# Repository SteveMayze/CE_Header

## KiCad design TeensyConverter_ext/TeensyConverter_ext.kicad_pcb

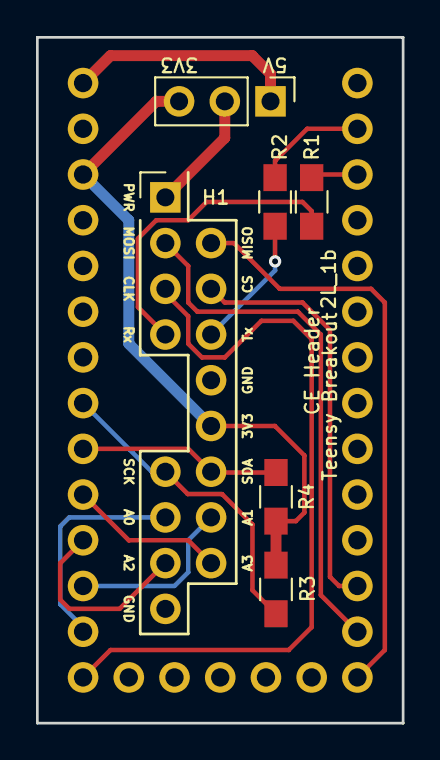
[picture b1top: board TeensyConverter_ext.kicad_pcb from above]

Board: 2 copper layers, 20.3 x 38.1 mm, 7 parts (1 on the bottom side), 18 nets.

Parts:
H1: CE_Header
P1: CONN_01X03; Pin_Header_Straight_1x03_Pitch2.54mm
R1, R2: R; R_0805_HandSoldering
R3, R4: 4.7kΩ; R_0805_HandSoldering
U1: Teensy-3.2; Teensy-32

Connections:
/3V3: H1.12, P1.3, R3.2, R4.2, U1.24
/5V: P1.1, U1.26
/AIO_0: H1.15, U1.14
/AIO_1: H1.16, U1.15
/AIO_2: H1.17, U1.16
/AIO_3: H1.18, U1.17
/DEVICE_RX: H1.7, R1.1
/DEVICE_TX: H1.8, R2.2
/GND: H1.10, H1.19, U1.27, U1.30
/I2C_DAT: H1.14, R4.1, U1.18
/I2C_SCLK: H1.13, R3.1, U1.19
/PWR_IO: H1.1, P1.2
/SPI_CLK: H1.5, U1.13
/SPI_CS: H1.6, U1.10
/SPI_MISO: H1.4, U1.12
/SPI_MOSI: H1.3, U1.11
/TEENCY_RX: R2.1, U1.0
/TEENCY_TX: R1.2, U1.1

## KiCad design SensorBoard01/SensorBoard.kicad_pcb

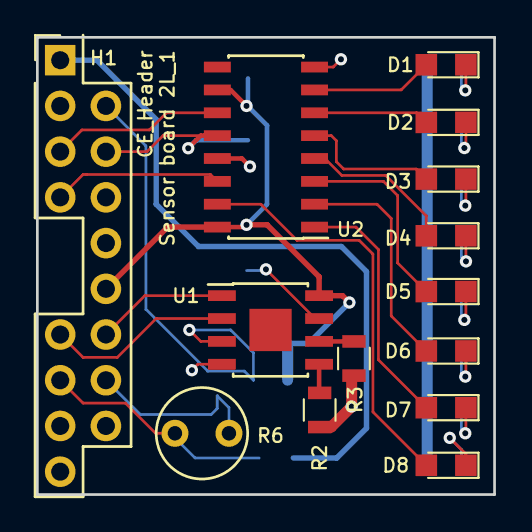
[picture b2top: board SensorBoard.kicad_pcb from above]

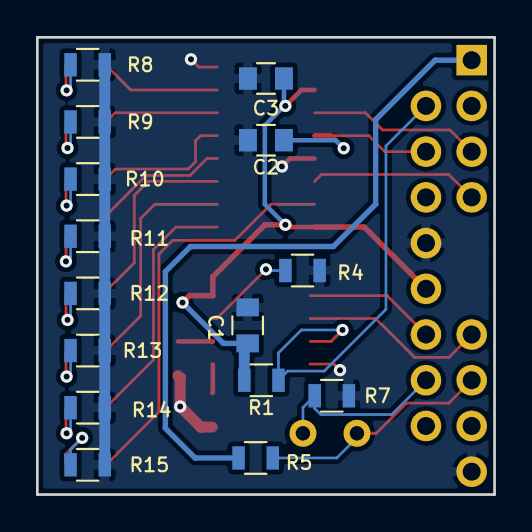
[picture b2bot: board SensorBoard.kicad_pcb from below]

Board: 2 copper layers, 25.4 x 25.4 mm, 29 parts (15 on the bottom side), 30 nets.

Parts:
C1, C2, C3: C; C_0805
D1, D2, D3, D4, D5, D6, D7, D8: LED; LED_0805
H1: CE_Header
R1, R2, R3, R4, R5, R7, R8, R9, R10, R11, R12, R13, R14, R15: R; R_0805
R6: Photo Resitor; Photo_Resistor_LDR01
U1: DS7505; SOIC-8-1EP_3.9x4.9mm_Pitch1.27mm
U2: 74HC595-PWR; SOIC-16_3.9x9.9mm_Pitch1.27mm

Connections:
/3V3: C1.2, C3.2, H1.12, R1.1, U1.8, U2.10, U2.16
/5V: H1.1, R5.1
/O.S: H1.4, R1.2, U1.3
/PR_BOT: H1.16, R6.2, R7.1
/PT_TOP: H1.15, R5.2, R6.1
/SCL: H1.13, U1.2
/SDA: H1.14, U1.1
/clockPin: H1.5, U2.11
/dataPin: H1.7, U2.14
/latchPin: C2.1, H1.6, U2.12
GND: C1.1, C2.2, C3.1, H1.10, H1.19, R2.2, R3.2, R4.2, R7.2, R8.1, R9.1, R10.1, R11.1, R12.1, R13.1, R14.1, R15.1, U1.4, U2.8, U2.13
unnamed: D1.1, R8.2
unnamed: D1.2, U2.7
unnamed: D2.1, R9.2
unnamed: D2.2, U2.6
unnamed: D3.1, R10.2
unnamed: D3.2, U2.5
unnamed: D4.1, R11.2
unnamed: D4.2, U2.4
unnamed: D5.1, R12.2
unnamed: D5.2, U2.3
unnamed: D6.1, R13.2
unnamed: D6.2, U2.2
unnamed: D7.1, R14.2
unnamed: D7.2, U2.1
unnamed: D8.1, R15.2
unnamed: D8.2, U2.15
unnamed: R2.1, U1.5
unnamed: R3.1, U1.6
unnamed: R4.1, U1.7

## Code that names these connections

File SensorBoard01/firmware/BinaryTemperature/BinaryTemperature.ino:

// DS7505 
// by Alexandre Coffignal <http://www. ... .com>

// Demonstrates use of the DS7505 library
// Reads data from an I2C/TWI DS7505 slave device

// Created 26 October 2010

#include <Wire.h>




//Pin connected to ST_CP of 74HC595
int latchPin = 10;
//Pin connected to SH_CP of 74HC595
int clockPin = 13;
////Pin connected to DS of 74HC595
int dataPin = 1;




void setup()
{
  Wire.begin();        // join i2c bus (address optional for master)
  Serial.begin(9600);  // start serial for output
  pinMode(latchPin, OUTPUT);
  pinMode(clockPin, OUTPUT);
  pinMode(dataPin, OUTPUT);
  digitalWrite(latchPin, LOW);
  shiftOut(dataPin, clockPin, MSBFIRST, 0x00); 
  digitalWrite(latchPin, HIGH);
}

void loop()
{

  float temperature = 0;
  Wire.beginTransmission(0x48);
  Wire.write(0x00);
  Wire.endTransmission();
  
  Wire.requestFrom(0x48, 2);
  if( 2<= Wire.available()){
    char temp_int = Wire.read();
    char temp_dec = Wire.read();

    float dec = (temp_dec >> 7) / 2.0;
    temperature = temp_int + dec;    
    Serial.printf("SAMPLE={%d, %d}, TEMPERATURE=%f\n", temp_int, temp_dec, temperature);
    
    digitalWrite(latchPin, LOW);
    shiftOut(dataPin, clockPin, LSBFIRST, temp_int);  
    digitalWrite(latchPin, HIGH);

}  
  delay(1000);

}

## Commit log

2017-03-11 Added the new directory for the sample header project
2017-03-11 Moved the CE Header files to their own directory
2017-03-18 Some corrections to the symbol
2017-03-26 CE Header associated with the Teensy and the layout started
2017-03-28 Created the layout and submitted to OSH Park
2017-03-30 Corrected the soldermask spec
2017-04-16 Created the schematic and base layout for the sensor board
2017-04-23 Completed the layout for the CE_Header sensor board
2017-06-03 Correction to footprint and resistor values
2017-06-04 Correction to the teensy adapter for the pull ups
2017-06-04 A change of mind on the LDR resistor divider
2017-08-03 Added a small layout to demonstrate the issue with the header on the backside
2017-08-09 Added the socket to complement the header
2018-01-17 Moved in the sample programs
2018-01-17 Added the datasheet for the Shift Register
2018-01-17 Corrected some library reference issues
2018-07-31 Update to rev5 KiCad
